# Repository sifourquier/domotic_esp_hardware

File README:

https://github.com/sifourquier/domotic_esp_hardware
hardware for use with

https://github.com/sifourquier/domotic_esp
and
https://github.com/sifourquier/domoticz_MQTTLite

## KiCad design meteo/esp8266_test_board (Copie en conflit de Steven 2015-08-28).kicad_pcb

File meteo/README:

Electronic for meteo sensors (Temperature Humidity Pressure)
Power by 1 or 2 battery 1.2V/1.5V or 5V (mini USB)
1 batterie R14 can spupply for more of 6 months if configured on static ip
 
FIXME
If use with only 1battery the stepup are to low current i have fix it by using 0x220uF on the power but work only if the connection time are low (use IP fix do not use dhcp)
If you use a rechargabel battery you can chage with connecting to usb but the heating of charge distorts the measure

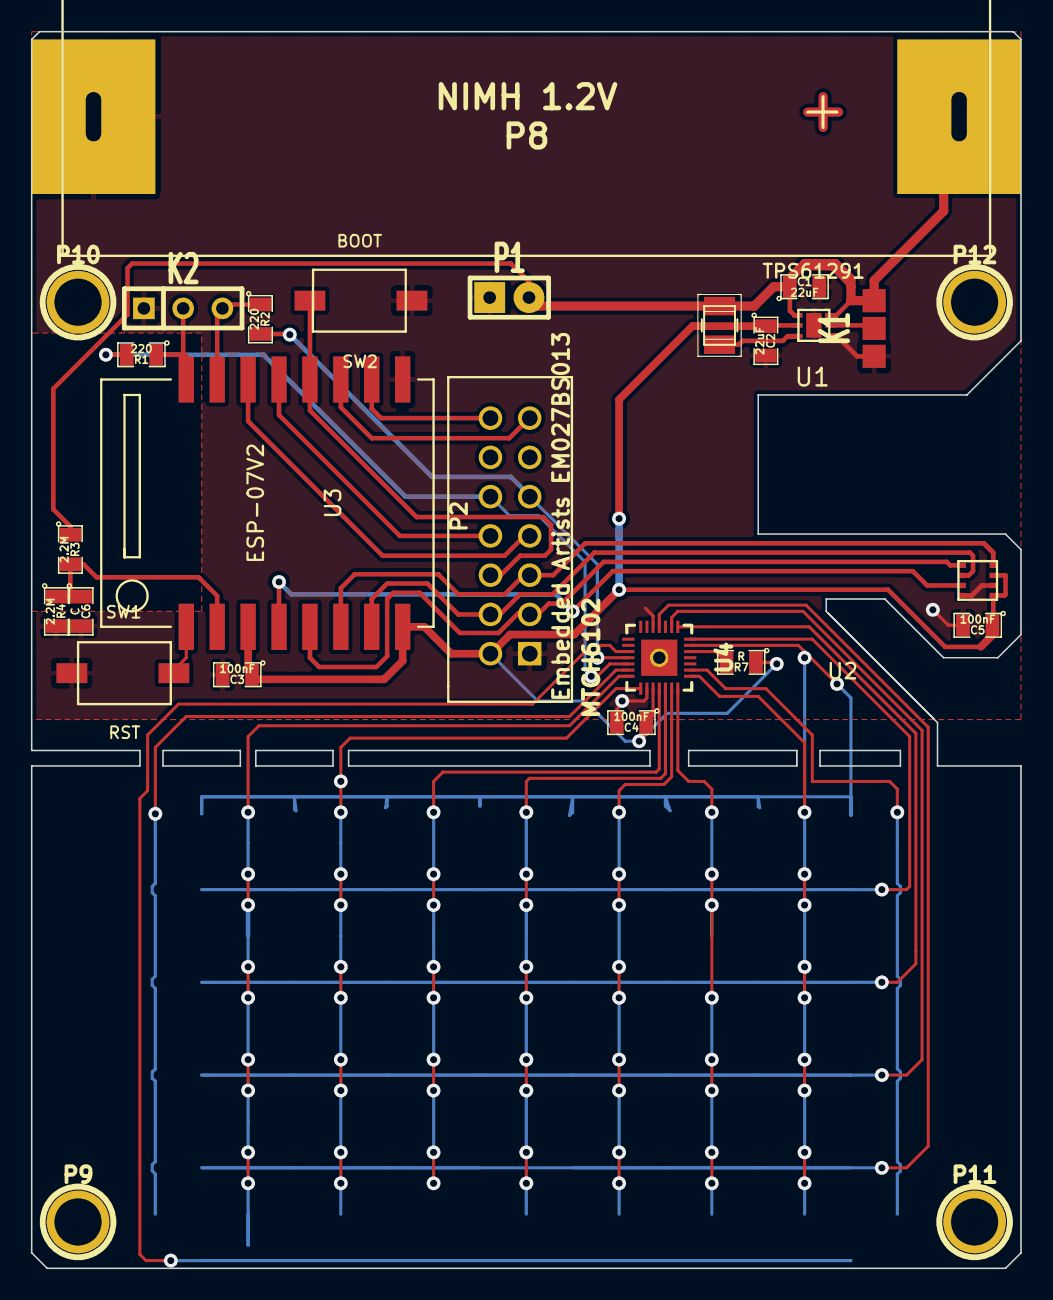
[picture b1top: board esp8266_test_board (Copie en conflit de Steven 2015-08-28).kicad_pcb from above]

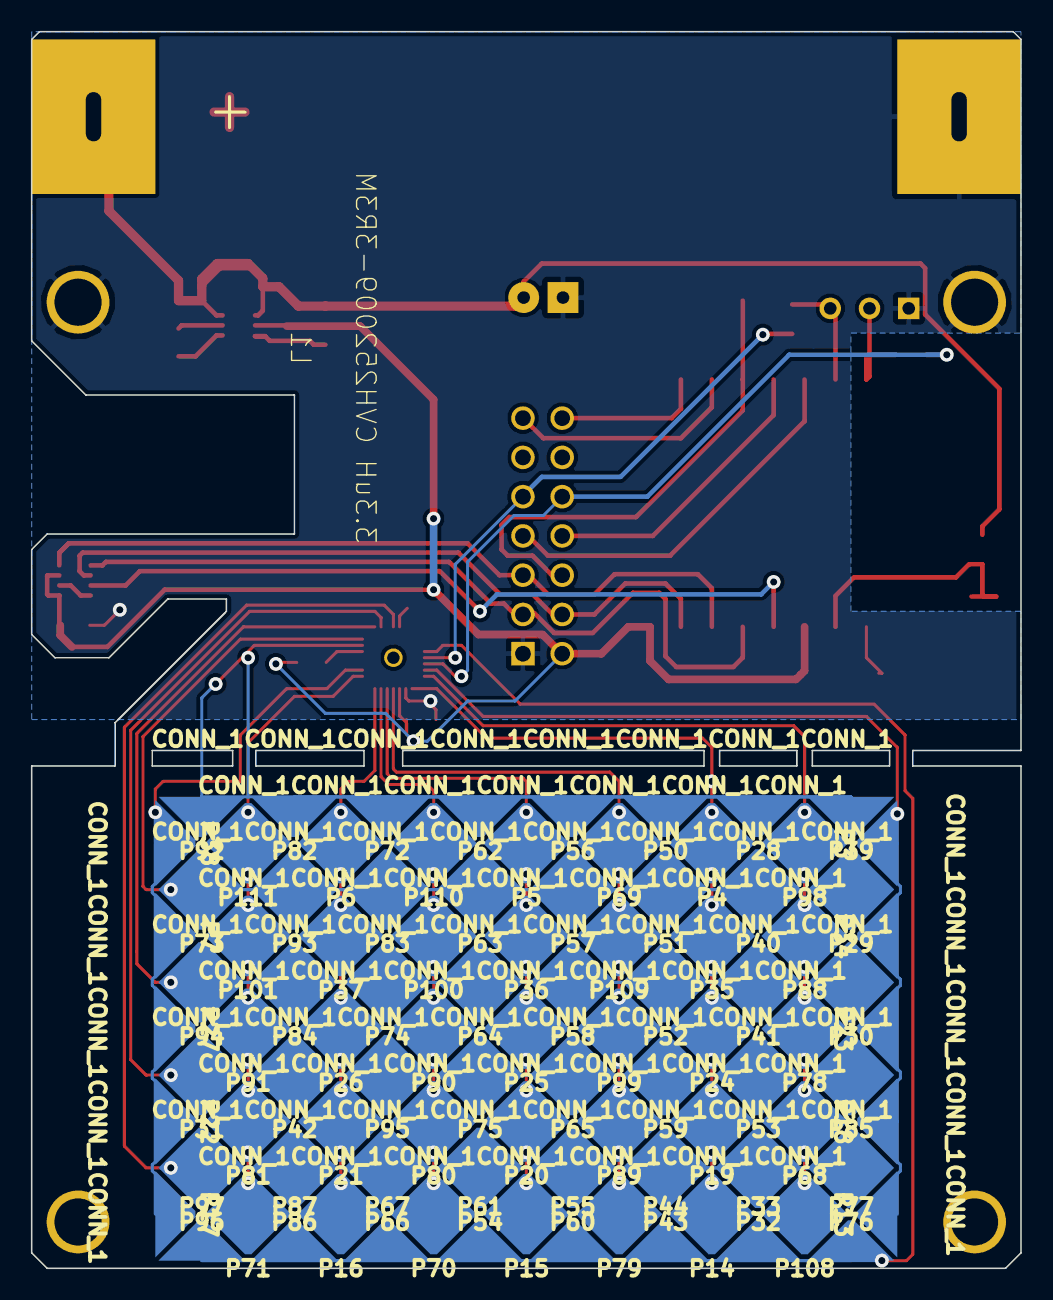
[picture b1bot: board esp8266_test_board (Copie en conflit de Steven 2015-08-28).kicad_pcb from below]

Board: 2 copper layers, 64.0 x 80.0 mm, 120 parts (93 on the bottom side), 36 nets.

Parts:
C1, C2: 22uF; SM0805
C3, C4, C5: 100nF; SM0805
C6: C; SM0805
K1: CONN_3; JUMP-3
K2: CONN_3; SIL-3
L1: 3.3uH CVH252009-3R3M; ipc-7351-inductor-INDC2520X220N
P1: Solar 1.5V; SIL-2
P2: Embedded Artists EM027BS013; pin_array_7x2
P3, P7, P13, P17, P18, P22, P23, P27, P28, P33, P34, P38, P39, P44, P50, P55, P56, P61, P62, P67, P72, P77, P82, P87, P92, P97: CONN_1; touch_4mm_demi
P4, P5, P6, P14, P15, P16, P19, P20, P21, P24, P25, P26, P29, P30, P31, P32, P35, P36, P37, P40, P41, P42, P43, P51, P52, P53, P54, P57, P58, P59, P60, P63, P64, P65, P66, P68, P69, P70, P71, P73, P74, P75, P76, P78, P79, P80, P81, P83, P84, P85, P86, P88, P89, P90, P91, P93, P94, P95, P96, P98, P99, P100, P101, P108, P109, P110, P111: CONN_1; touch_4mm_chenfrain
P8: NIMH 1.2V; AA
P9, P10, P11, P12: DRILL; 1pin
R1, R2: 220; SM0805
R3, R4: 2.2M; SM0805
R7: R; SM0805
SW1: RST; SW_PUSH_SMD_2pad
SW2: BOOT; SW_PUSH_SMD_2pad
U1: TPS61291; PWSON-N6
U2: BME280; LGA8_2.5×2.5
U3: ESP-07V2; ESP-07v2
U4: MTCH6102; UQFN28

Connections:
+2.5V: C2.1, C3.1, C4.1, C5.1, P2.2, R7.1, U1.2, U2.6, U2.8, U3.3, U3.8, U4.17
/ADC: C6.1, R3.2, R4.1, U3.2
/CS_BME: U2.2, U3.4
/EPD_BORDER: P2.8, U3.13
/EPD_BUSY: P2.7, U3.14
/EPD_CS: P2.6, SW2.2, U3.12
/EPD_DISCHARGE: P2.14, U3.10
/EPD_ON: P2.13, U3.11
/MISO: P2.5, U2.5, U3.6
/MOSI: P2.4, U2.3, U3.7
/RX: K2.3, R2.1, U3.15
/SCL: P2.9, R2.2, U4.11
/SCLK: P2.3, U2.4, U3.5
/SDA: P2.10, R1.2, U4.12
/TX: K2.2, R1.1, U3.16
/X1: P3.1, P13.1, P18.1, P23.1, P34.1, U4.13
/X2: P68.1, P78.1, P88.1, P98.1, P108.1, U4.14
/X3: P4.1, P14.1, P19.1, P24.1, P35.1, U4.15
/X4: P69.1, P79.1, P89.1, P99.1, P109.1, U4.18
/X5: P5.1, P15.1, P20.1, P25.1, P36.1, U4.19
/X6: P70.1, P80.1, P90.1, P100.1, P110.1, U4.20
/X7: P6.1, P16.1, P21.1, P26.1, P37.1, U4.21
/X8: P71.1, P81.1, P91.1, P101.1, P111.1, U4.22
/X9: P7.1, P17.1, P22.1, P27.1, P38.1, U4.23
/Y1: P28.1, P39.1, P50.1, P56.1, P62.1, P72.1, P82.1, P92.1, U4.27
/Y2: P29.1, P40.1, P51.1, P57.1, P63.1, P73.1, P83.1, P93.1, U4.28
/Y3: P30.1, P41.1, P52.1, P58.1, P64.1, P74.1, P84.1, P94.1, U4.1
/Y4: P31.1, P42.1, P53.1, P59.1, P65.1, P75.1, P85.1, P95.1, U4.2
/Y5: P32.1, P43.1, P54.1, P60.1, P66.1, P76.1, P86.1, P96.1, U4.4
/Y6: P33.1, P44.1, P55.1, P61.1, P67.1, P77.1, P87.1, P97.1, U4.10
/nRST: SW1.2, U3.1
GND: C1.2, C2.2, C3.2, C4.2, C5.2, C6.2, K1.1, K2.1, P1.1, P2.1, P8.1, P10.1, P12.1, R4.2, SW1.1, SW2.1, U1.6, U2.1, U2.7, U3.9, U4.5, U4.16
unnamed: L1.2, U1.1
unnamed: C1.1, K1.3, L1.1, P1.2, P8.2, R3.1, U1.3, U1.4
unnamed: R7.2, U4.26
unnamed: K1.2, U1.5

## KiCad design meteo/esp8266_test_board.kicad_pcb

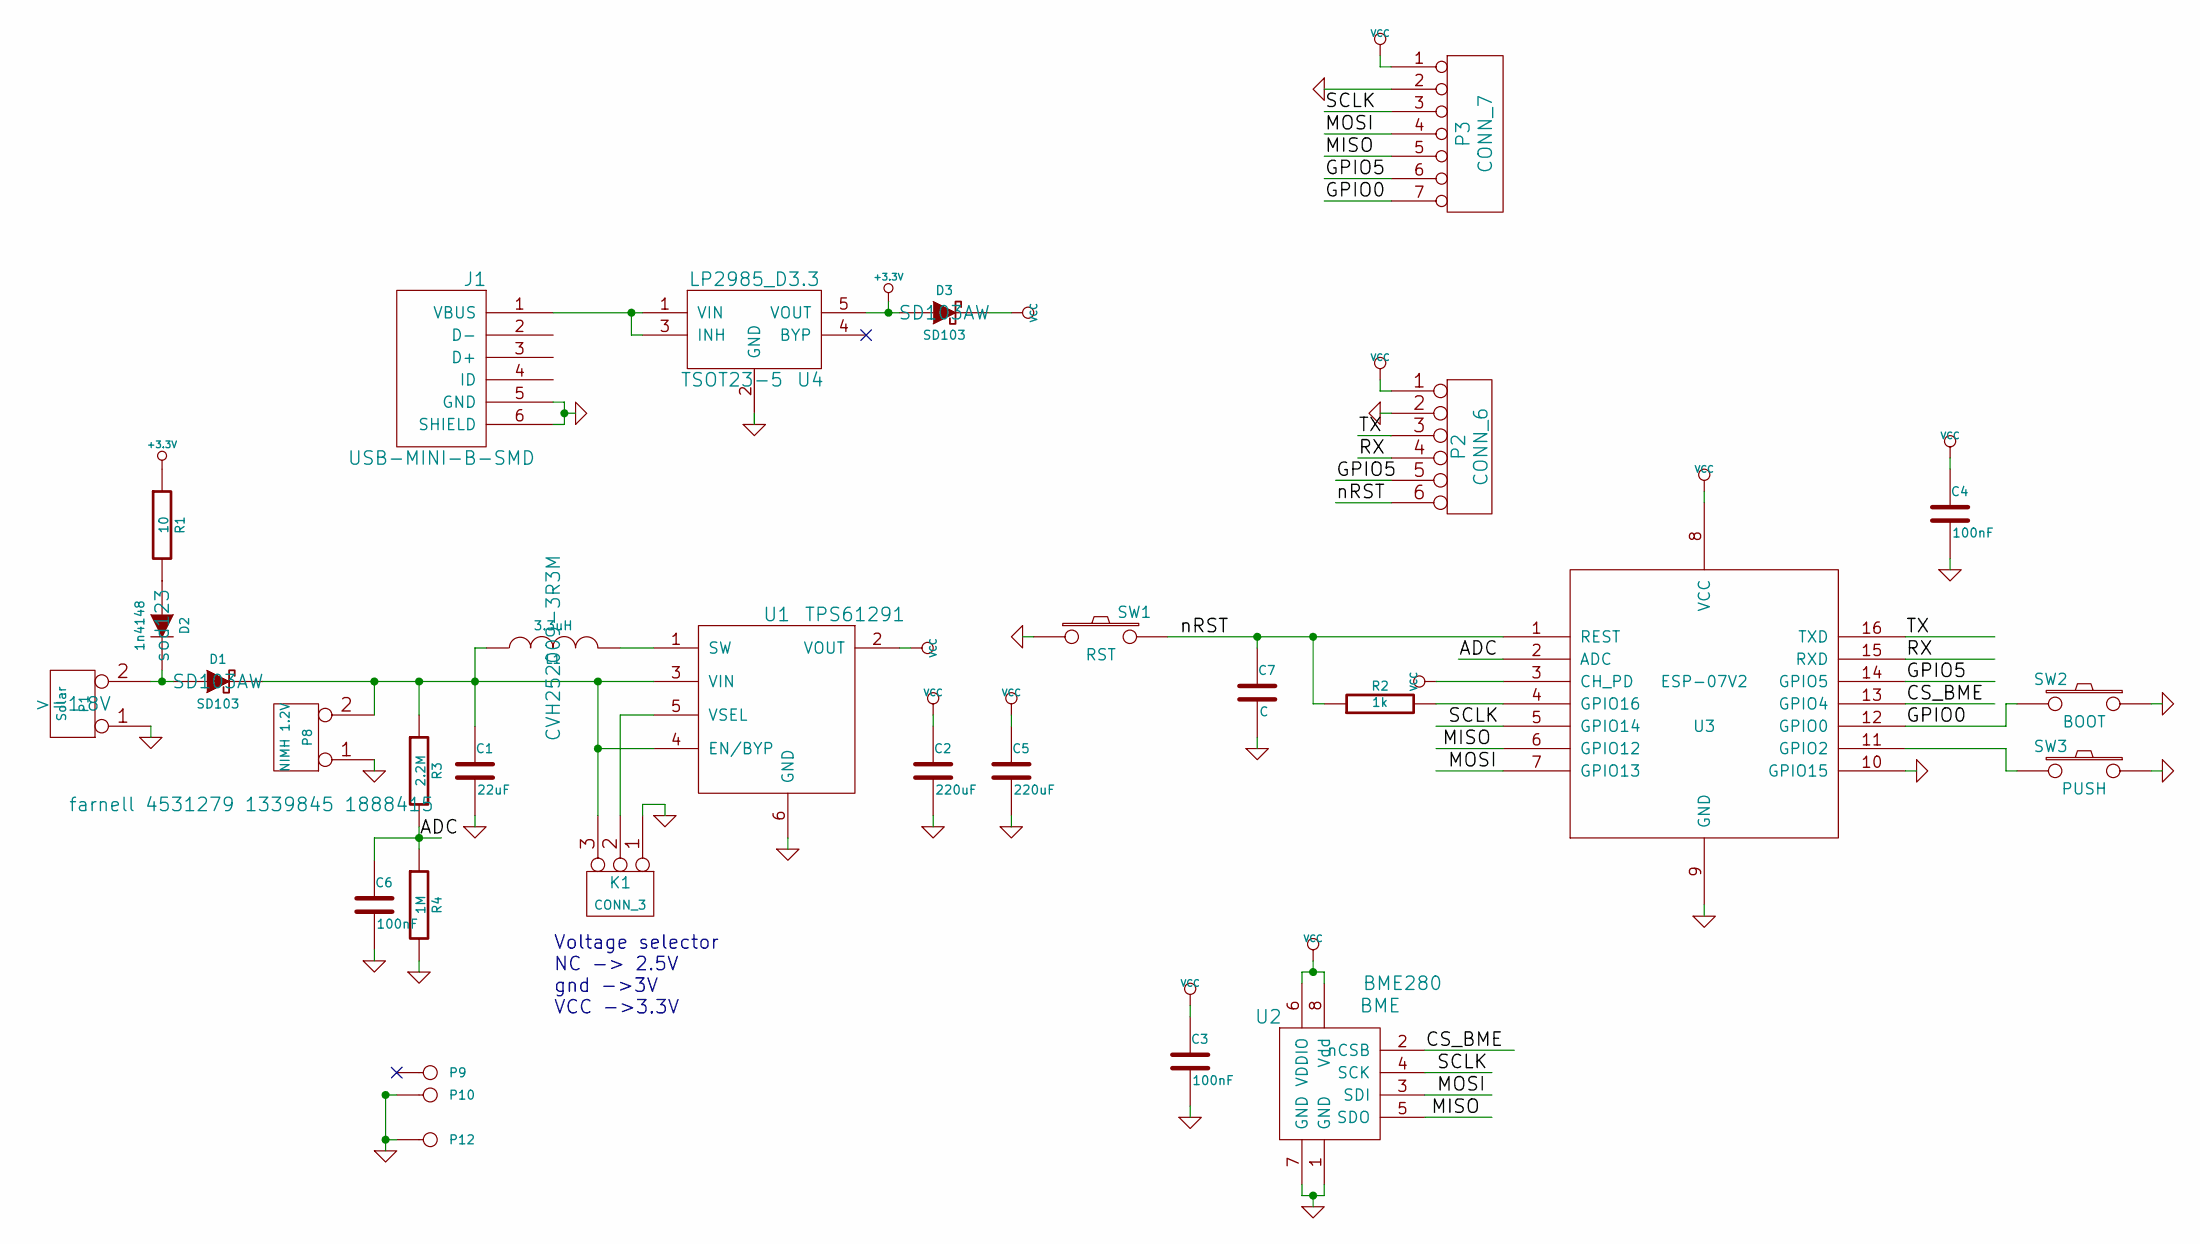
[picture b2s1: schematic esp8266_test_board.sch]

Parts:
C1: 22uF
C2, C5: 220uF
C3, C4, C6: 100nF
C7: C
D1, D3: SD103
D2: 1n4148
J1: USB-MINI-B-SMD
K1: CONN_3
L1: 3.3uH
P1: Solar
P2: CONN_6
P3: CONN_7
P8: NIMH 1.2V
P9, P10, P12: DRILL
R1: 10
R2: 1k
R3: 2.2M
R4: 1M
SW1: RST
SW2: BOOT
SW3: PUSH
U1: TPS61291
U2: BME
U3: ESP-07V2
U4: LP2985_D3.3; TSOT23-5

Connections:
+3.3V: D3.1 (A), R1.1, U4.5 (VOUT)
/ADC: C6.1, R3.2, R4.1, U3.2 (ADC)
/CS_BME: U2.2 (nCSB), U3.13 (GPIO4)
/GPIO0: P3.7, SW2.2, U3.12 (GPIO0)
/GPIO5: P2.5, P3.6, U3.14 (GPIO5)
/MISO: P3.5, U2.5 (SDO), U3.6 (GPIO12)
/MOSI: P3.4, U2.3 (SDI), U3.7 (GPIO13)
/RX: P2.4, U3.15 (RXD)
/SCLK: P3.3, U2.4 (SCK), U3.5 (GPIO14)
/TX: P2.3, U3.16 (TXD)
/nRST: C7.1, P2.6, R2.1, SW1.2, U3.1 (REST)
GND: C1.2, C2.2, C3.2, C4.2, C5.2, C6.2, C7.2, J1.5 (GND), J1.6 (SHIELD), K1.1, P1.1, P2.2, P3.2, P8.1, P10.1, P12.1, R4.2, SW1.1, SW2.1, SW3.1, U1.6 (GND), U2.1 (GND), U2.7 (GND), U3.9 (GND), U3.10 (GPIO15), U4.2 (GND)
unnamed: D2.1 (A), R1.2
unnamed: J1.1 (VBUS), U4.1 (VIN), U4.3 (INH)
unnamed: R2.2, U3.4 (GPIO16)
unnamed: D1.1 (A), D2.2 (K), P1.2 (PM)
unnamed: SW3.2, U3.11 (GPIO2)
unnamed: K1.2 (PM), U1.5 (VSEL)
unnamed: L1.2, U1.1 (SW)
unnamed: C1.1, D1.2 (K), K1.3, L1.1, P8.2 (PM), R3.1, U1.3 (VIN), U1.4 (EN/BYP)
VCC: C2.1, C3.1, C4.1, C5.1, D3.2 (K), P2.1, P3.1, U1.2 (VOUT), U2.6 (VDDIO), U2.8 (Vdd), U3.3 (CH_PD), U3.8 (VCC)

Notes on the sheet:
Voltage selector NC -> 2.5V gnd ->3V VCC ->3.3V

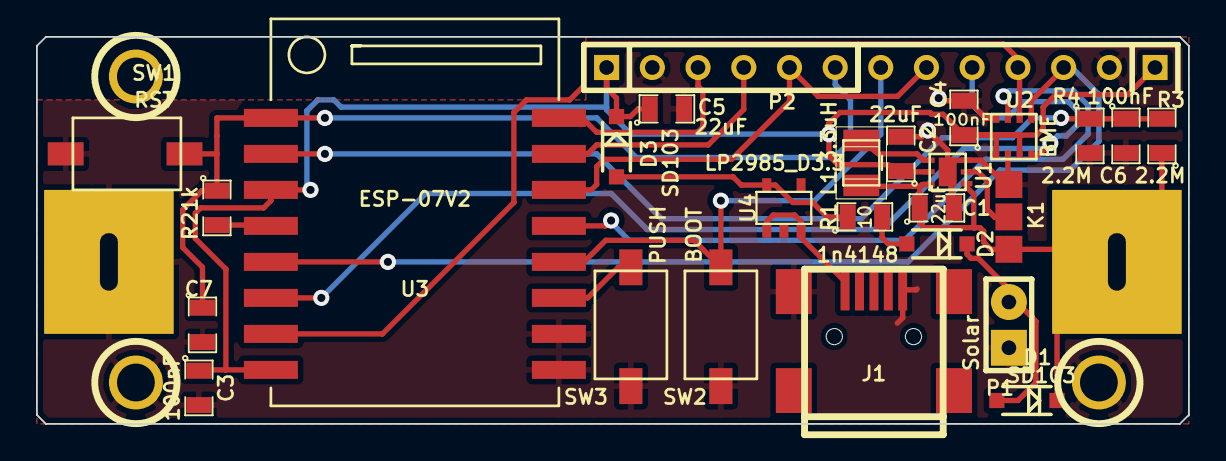
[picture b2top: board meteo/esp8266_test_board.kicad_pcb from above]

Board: 2 copper layers, 64.0 x 21.5 mm, 31 parts (1 on the bottom side), 21 nets.

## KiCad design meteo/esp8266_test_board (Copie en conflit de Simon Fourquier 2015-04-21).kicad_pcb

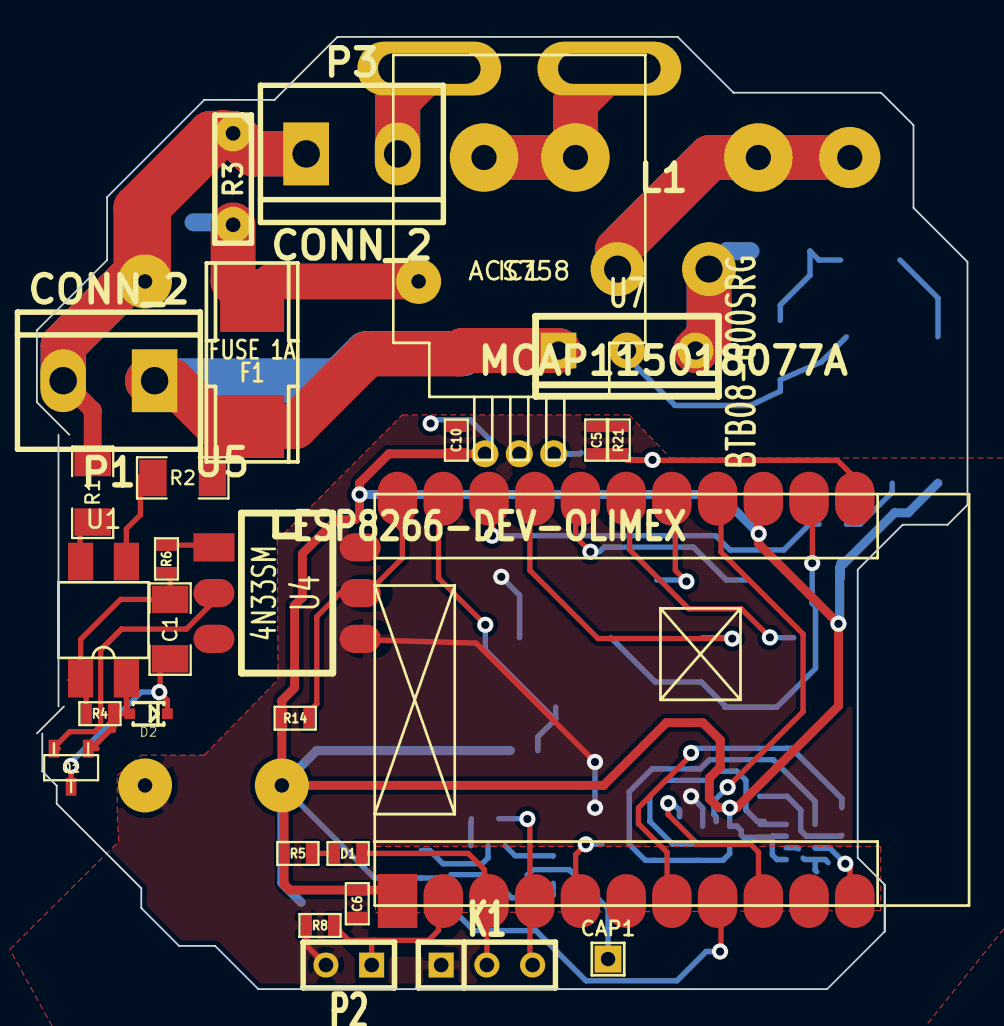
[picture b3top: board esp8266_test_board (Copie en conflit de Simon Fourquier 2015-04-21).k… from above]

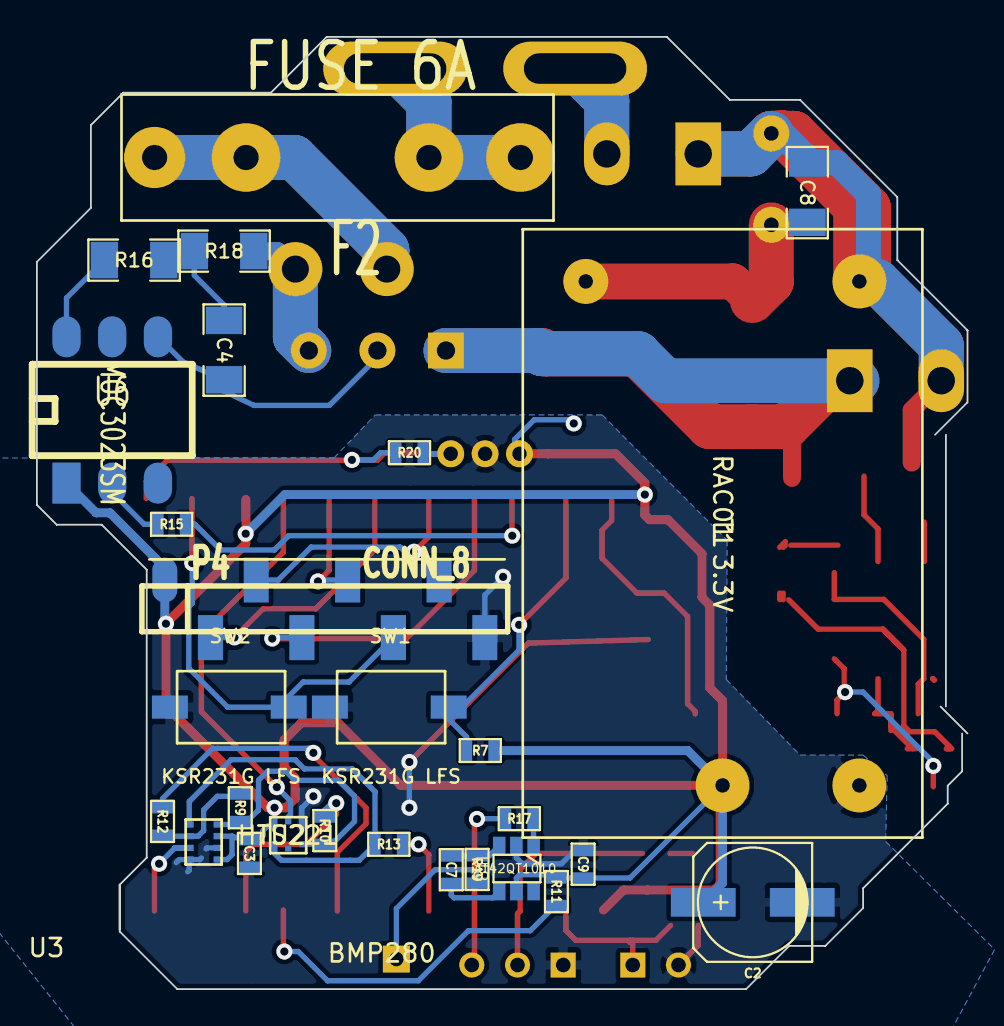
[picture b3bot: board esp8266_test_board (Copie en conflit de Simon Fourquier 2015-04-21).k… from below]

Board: 2 copper layers, 51.7 x 52.9 mm, 55 parts (27 on the bottom side), 47 nets.

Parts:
C1: 10uF 16v; SM1206
C2: 330uF; c_elec_6.3x7.7
C3, C6, C9, C10: 100nF; SM0603
C4, C8: 47nF; SM1206
C5: nc; SM0603
C7: 22nF?; SM0603
CAP1: CONN_1; SIL-1
D1: LED_blue; SM0603
D2: BAS 21-03W E6327; SOD323-REFLOW
F1: FUSE 1A; FSUPCMS
F2: FUSE 6A; FUSE7-20
IC1: ACS758; PFF
K1: CONN_3; SIL-3
L1: MCAP115018077A; self
P1, P3: CONN_2; bornier2
P2: CONN_2; SIL-2
P4: CONN_8; SIL-8_smd
Q1: BC847B; sot23
R1, R2: 220k; SM1206
R3: MCSR431K07DS; C2
R4, R20: 22k; SM0603
R5: 470E; SM0603
R6, R9, R19: 1k; SM0603
R7: 10K; SM0603
R8: 0.1; SM0603
R10, R12, R13: 0?; SM0603
R11, R21: 10k; SM0603
R14: 4.7k; SM0603
R15: 330; SM0603
R16: 330; SM1206
R17: 1K; SM0603
R18: 470; SM1206
SW1, SW2: KSR231G LFS; SW_PUSH_SMD_2pad
T1: RAC01 3.3V; RAC01
U1: MB8S
U2: HTS221; hlga-6l
U3: BMP280; LGA8_2.0×2.5
U4: 4N33SM; DIP-6__300_SMD
U5: ESP8266-DEV-OLIMEX; ESP8266_olimex_dev
U6: MOC3023SM; DIP-6__300_SMD
U7: BTB08-600SRG; TO220_VERT
U8: AT42QT1010; SOT23_6

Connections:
+3.3V: C2.1, C3.1, C6.1, C9.1, C10.1, IC1.1, P4.1, R5.1, R7.1, R11.1, R14.1, T1.4, U2.1, U3.6, U3.8, U5.1, U5.14, U6.1, U8.5
/230_0: F1.1, P1.1, R2.1, U7.1
/230_1: L1.2, R18.2, U7.2
/230_3: F2.2, IC1.4
/230_4: C8.2, F1.2, R3.2, T1.2
/230_10: R1.2, U1.4
/230_11: R2.2, U1.3
/ACN: C8.1, P1.2, P3.1, R1.1, R3.1, T1.1
/ACN_FUSS: F2.1, L1.1
/CAP: R17.1, U8.1
/RX/CAP: K1.3, R17.2, U5.4
/TCLK: P4.3, U5.18
/TDI: P4.5, U5.16
/TDO: P4.4, U5.19
/TMS: P4.2, U5.17
/TRIAC: R15.1, U5.20
/TX: D1.2, K1.2, U5.3
/adc: C5.1, R20.2, R21.1, U5.12
/nCS_BMP: U3.2, U5.11
/nCS_HTS: U2.6, U5.15
/nRST: P4.6, SW2.2, U5.13
/nZeroCross: R14.2, U4.5, U5.22
GND: C2.2, C3.2, C5.2, C6.2, C9.2, C10.2, IC1.2, K1.1, P2.2, P4.8, R8.1, R21.2, SW1.1, SW2.1, T1.3, U2.5, U3.1, U3.7, U4.4, U8.2
unnamed: R13.1, U2.2, U3.4
unnamed: R9.2, R12.1, U3.3
unnamed: R7.2, SW1.2, U5.21
unnamed: D1.1, R5.2
unnamed: P2.1, R8.2, U5.2
unnamed: C7.2, U8.4
unnamed: C1.2, D2.1, Q1.3
unnamed: C7.1, R19.2, U8.3
unnamed: IC1.3, R20.1
unnamed: R13.2, U5.5
unnamed: R12.2, U5.7
unnamed: IC1.5, P3.2
unnamed: Q1.2, U4.2
unnamed: R10.2, U5.9
unnamed: CAP1.1, R19.1
unnamed: R15.2, U6.2
unnamed: R6.2, U4.1
unnamed: D2.2, Q1.1, R4.2, U1.2
unnamed: C1.1, R4.1, R6.1, U1.1
unnamed: C4.2, U6.4, U7.3
unnamed: C4.1, R16.2, R18.1
unnamed: R16.1, U6.6
unnamed: R9.1, R10.1, U2.4, U3.5
unnamed: R11.2, U5.8

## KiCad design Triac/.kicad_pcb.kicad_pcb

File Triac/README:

Electronic for controling 230V (triac) and mesuring consumption
Use for 230V (light control)
Use for pilot wire radiator
If add an external power supply and mosN you can use for low voltage light (for exemple 36V led)
by adding external quadratur sensor, powwer suply and Hbridge(DRV8871) you can control a motor (for exemple awning)

fixme the VTX-214-001-103 need be soldering befor esp8266
if creat a new pcb try to change VTX-214-001-103 by VTX-214-001-303 (for reduct consumption)

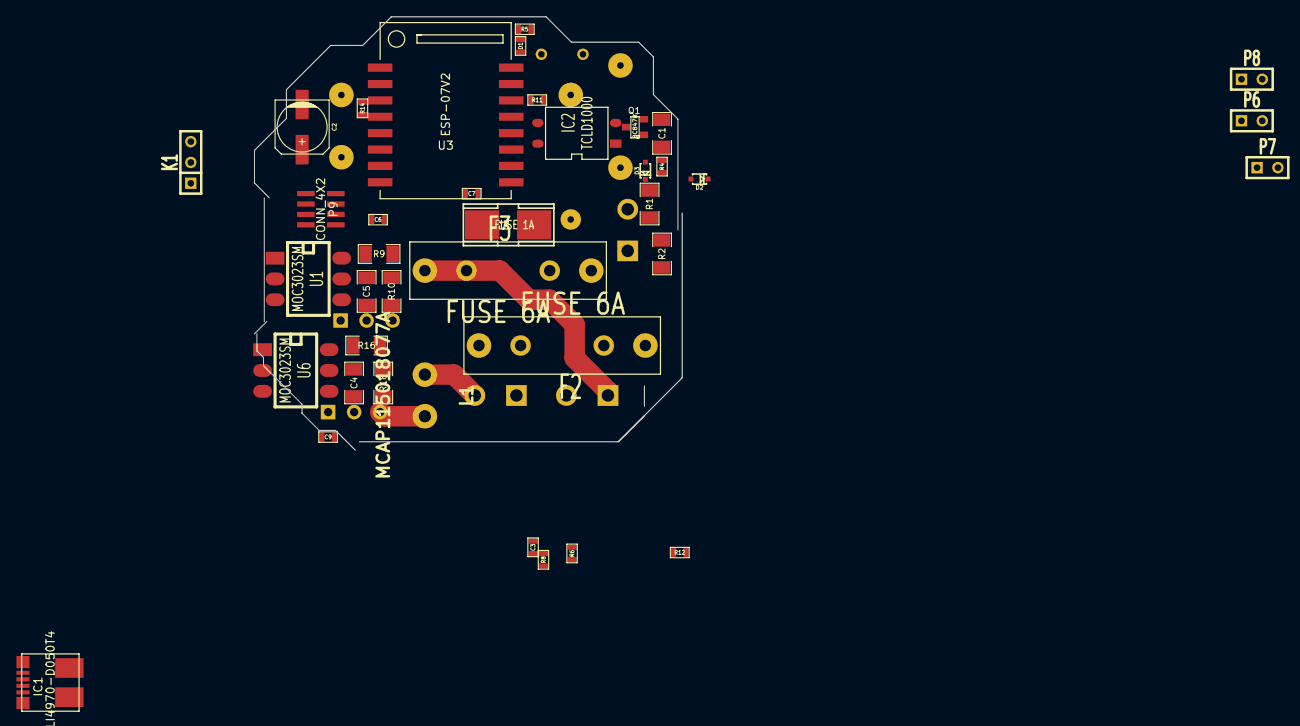
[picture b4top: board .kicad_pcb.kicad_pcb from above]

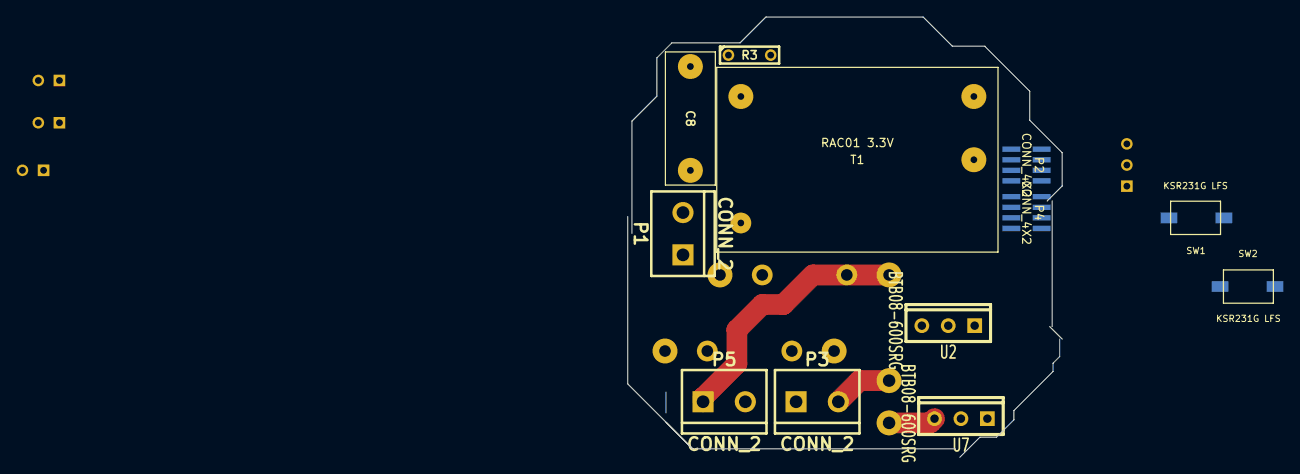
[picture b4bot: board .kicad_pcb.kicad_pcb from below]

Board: 2 copper layers, 52.2 x 52.9 mm, 51 parts (12 on the bottom side), 40 nets.

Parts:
C1: 1uF 16v; SM1206
C2: 330uF; c_elec_6.3x7.7
C3, C6, C9: 100nF; SM0603
C4, C5: 47nF; SM1206
C7: 10uF; SM0603
C8: 47nF; C230v
D1: LED_blue; SM0603
D2, D3: BAS 21-03W E6327; SOD323-REFLOW
F1: FUSE 1A; FSUPCMS
F2, F3: FUSE 6A; FUSE7-20
IC1: TLI4970-D050T4; PG-TISION-8-1
IC2: TCLD1000; DIP-4_long_SMD
K1: CONN_3; SIL-3
L1: MCAP115018077A; self
P1, P3, P5: CONN_2; bornier2
P2, P4, P9: CONN_4X2; conn_2x4_1.27_smd
P6, P7, P8: CONN_2; SIL-2
Q1: BC847B; SOT23
R1, R2: 1M; SM1206
R3: MCSR431K07DS; C2
R4: 22k; SM0603
R5: 470E; SM0603
R6: 27; SM0603
R8, R11, R12: R; SM0603
R9, R16: 330; SM1206
R10, R18: 470; SM1206
R14: 10k; SM0603
SW1, SW2: KSR231G LFS; SW_PUSH_SMD_2pad
T1: RAC01 3.3V; RAC01
U1, U6: MOC3023SM; DIP-6__300_SMD
U2, U7: BTB08-600SRG; TO220_VERT
U3: ESP-07V2; ESP-07v2

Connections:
+3.3V: C2.1, C3.1, C6.1, P2.7, P4.7, P9.7, R5.1, R12.1, R14.1, T1.4, U1.1, U3.3, U3.8, U6.1
/230_0: F1.1, P1.1, R2.1, U2.1, U7.1
/230_1: L1.2, R18.2, U7.2
/230_2: F2.2, F3.1, IC1.8
/230_3: F2.1, P3.1
/230_4: C8.2, F1.2, R3.2, T1.2
/230_5: P5.2, R10.2, U2.2
/230_10: D3.1, R1.2
/230_11: D2.2, Q1.1, R2.2, R4.2
/ACN: C8.1, IC1.7, P1.2, R1.1, R3.1, T1.1
/ACN_FUSS: L1.1, P3.2
/GPIO0: P4.5, SW1.2, U3.12
/MISO: IC1.3, P2.6, P4.6, P9.6, U3.6
/MOSI: P2.4, P4.4, P9.4, U3.7
/NCS_EXT1.1: K1.3, P4.3, U3.15
/NCS_EXT2.1: P2.3, U3.4
/NCS_EXT2.2: D1.2, K1.2, P2.5, U3.16
/NCS_TLI: IC1.5, U3.10
/NCS_TOUCH.1: P9.5, U3.11
/SCLK: IC1.4, P2.8, P4.8, P9.8, U3.5
/TRIAC1: R11.2, U3.14
/TRIAC2: R8.2, U3.13
/nRST: SW2.2, U3.1
/nZeroCross: IC2.4, R14.2, U3.2
GND: C2.2, C3.2, C6.2, C7.2, C9.2, IC1.1, IC2.3, K1.1, P2.1, P2.2, P4.1, P4.2, P6.1, P6.2, P7.1, P7.2, P8.1, P8.2, P9.1, P9.2, SW1.1, SW2.1, T1.3, U3.9
unnamed: C5.2, U1.4, U2.3
unnamed: C5.1, R9.2, R10.1
unnamed: R9.1, U1.6
unnamed: R8.1, U1.2
unnamed: F3.2, P5.1
unnamed: IC2.1, R6.2
unnamed: IC2.2, Q1.3
unnamed: R16.1, U6.6
unnamed: R11.1, U6.2
unnamed: C4.1, R16.2, R18.1
unnamed: C7.1, C9.1, IC1.2, R12.2
unnamed: D1.1, R5.2
unnamed: C4.2, U6.4, U7.3
unnamed: C1.2, D2.1, Q1.2
unnamed: C1.1, D3.2, R4.1, R6.1

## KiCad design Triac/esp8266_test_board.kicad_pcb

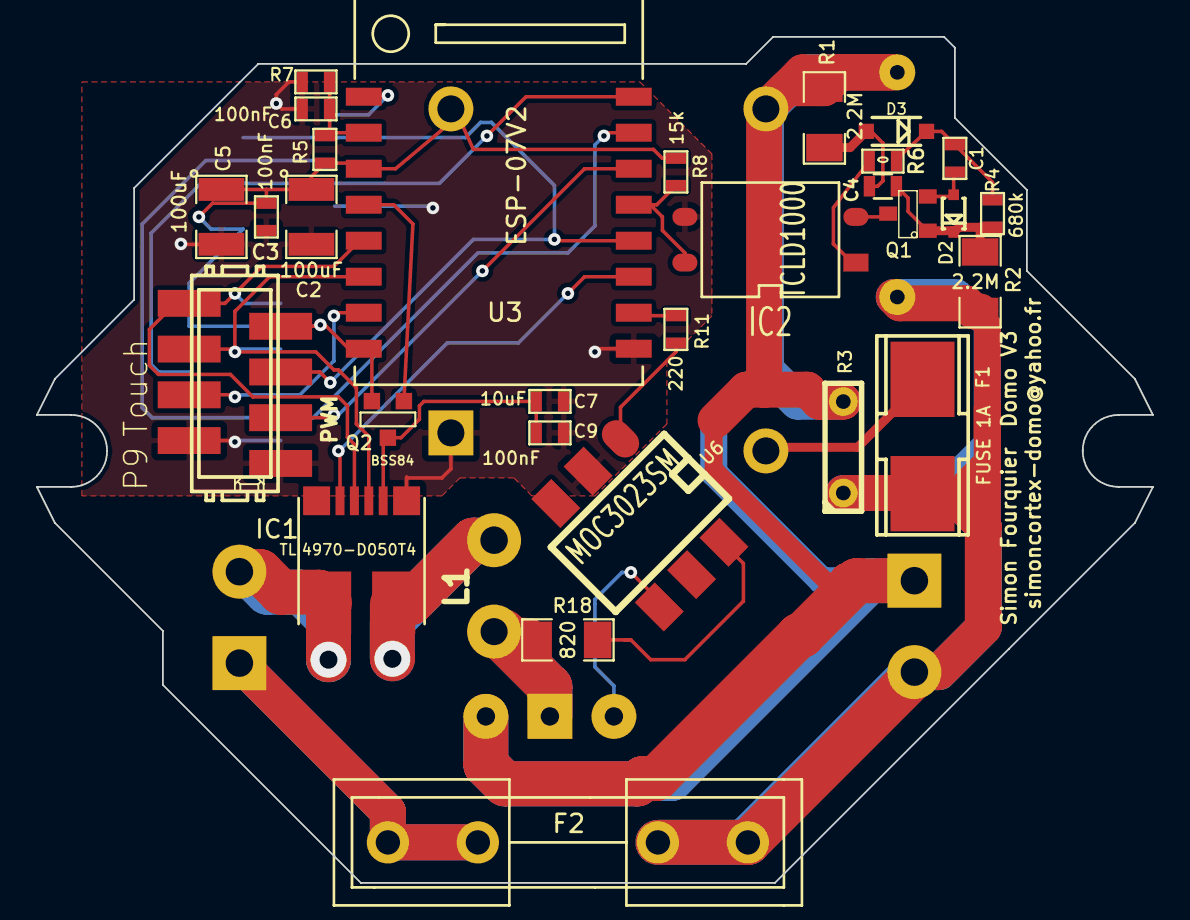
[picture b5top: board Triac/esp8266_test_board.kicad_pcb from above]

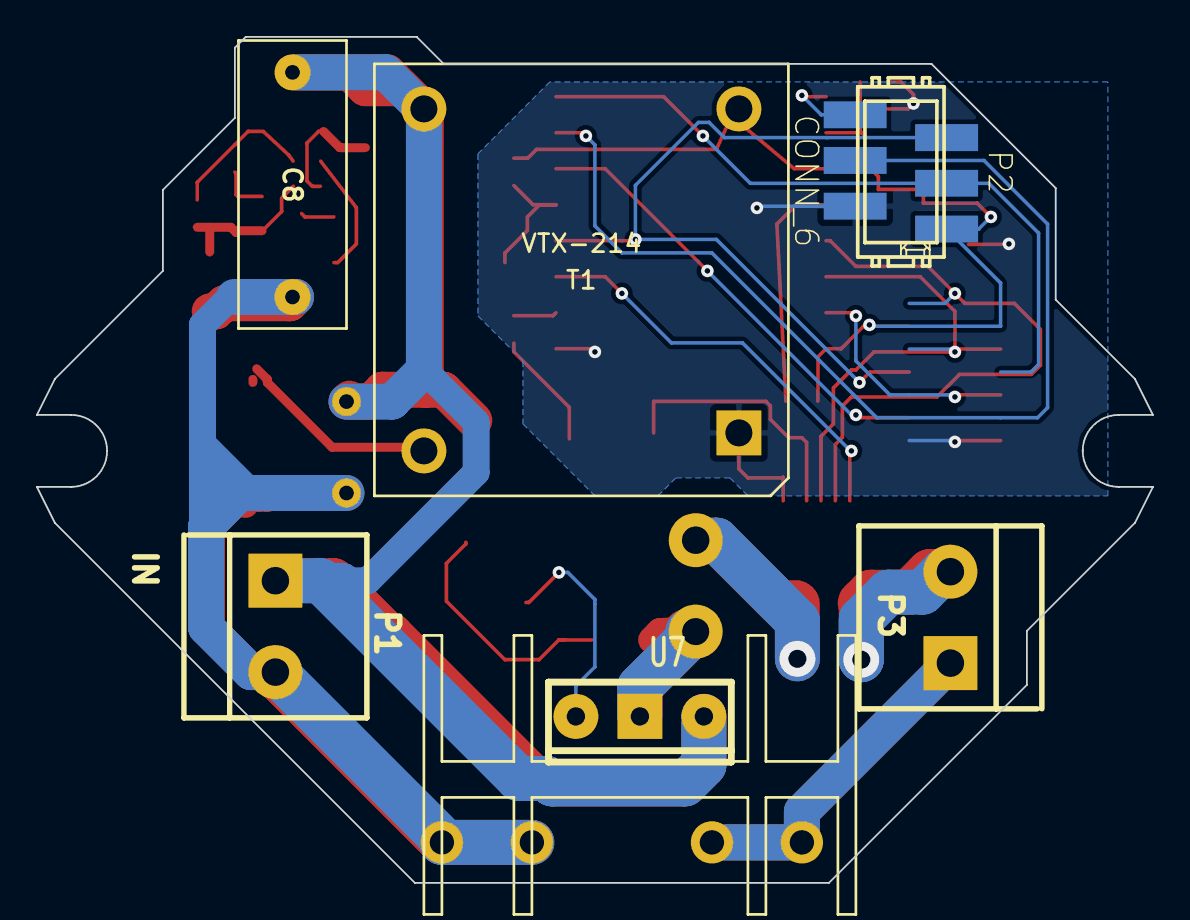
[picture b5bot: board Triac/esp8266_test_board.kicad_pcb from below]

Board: 2 copper layers, 62.0 x 47.0 mm, 36 parts (6 on the bottom side), 32 nets.

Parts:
C1: 100nF 10v; SM0603
C2, C5: 100uF; SM1210
C3, C6, C9: 100nF; SM0603
C4: 100pf 10v; R_0603
C7: 10uF; SM0603
C8: 47nF; C230v
D2: BAS 21-03W E6327; SOD323-REFLOW
D3: RR255M-400TR; SOD123
F1: FUSE 1A; FSUPCMS
F2: FUSE 6A; Fuseholder5x20_horiz_open_inline_Type-I
IC1: TLI4970-D050T4; PG-TISION-8-1
IC2: TCLD1000; DIP-4_long_SMD
L1: 2124-V-RC; self
P1: IN; bornier2_230v
P2: CONN_6; con-amp-micromatch-MMT-SMD-6
P3: OUT; bornier2_230v
P9: Touch; con-amp-micromatch-MMT-SMD-8
Q1: BC847B; SOT23
Q2: BSS84; SOT23GDS
R1, R2: 2.2M; SM1206
R3: MCSR431K07DS; C2
R4: 680k; SM0603
R5: 56k; SM0603
R6: 0; SM0603
R7: NTC 10k (ntcs0805E3103JMT); SM0603
R8: 15k; SM0603
R11: 220; SM0603
R18: 820; SM1206
T1: VTX-214; VTX-214-001-103
U3: ESP-07V2; ESP-07v2_small
U6: MOC3023SM; DIP-6__300_SMD
U7: BTA312-600B; TO220_VERT_230V_rad

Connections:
+3.3V: C2.1, C3.1, C5.1, P2.1, P9.7, Q2.S, R5.1, R8.1, T1.2, U3.3, U3.8
/230_1: L1.2, R18.2, U7.2
/230_2: IC1.7, P3.2
/230_3: F2.1, P3.1
/ACL: C8.2, P1.1, R1.1, R3.2, T1.3, U7.1
/ACN: C8.1, F1.1, F2.2, P1.2, R2.1, R3.1
/ACN_FUSS: IC1.8, L1.1
/ADC: C6.1, R5.2, R7.1, U3.2
/EN_Curent: Q2.G, U3.4
/GPIO0: P2.5, P9.5, U3.12
/MISO: IC1.3, P9.6, U3.6
/MOSI: P9.4, U3.7
/NCS_EXT1.1: P2.4, U3.15
/NCS_EXT1.2: P2.3, U3.16
/NCS_EXT2.0: P9.3, U3.14
/NCS_TLI: IC1.5, U3.11
/SCLK: IC1.4, P9.8, U3.5
/TRIAC1: R11.2, U3.10
/nRST: P2.6, U3.1
/nZeroCross: IC2.4, R8.2, U3.13
GND: C2.2, C3.2, C5.2, C6.2, C7.2, C9.2, IC1.1, IC2.3, P2.2, P9.1, P9.2, R7.2, T1.1, U3.9, U6.2
unnamed: C1.1, D3.2, R4.1, R6.1
unnamed: C1.2, D2.1, Q1.2
unnamed: C4.1, D3.1, R1.2
unnamed: C4.2, D2.2, Q1.1, R2.2, R4.2
unnamed: C7.1, C9.1, IC1.2, Q2.D
unnamed: F1.2, T1.4
unnamed: IC2.1, R6.2
unnamed: IC2.2, Q1.3
unnamed: R11.1, U6.1
unnamed: R18.1, U6.6
unnamed: U6.4, U7.3

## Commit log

2017-10-28 add readme
